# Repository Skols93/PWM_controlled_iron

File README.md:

# PWM_controlled_iron
PCB in Eagle EDA 

Measuring temperature with MAX6675 with Arduino UNO.Using MOSFET to control the temperature of a soldering iron using PID controller implemented in Arduino UNO.

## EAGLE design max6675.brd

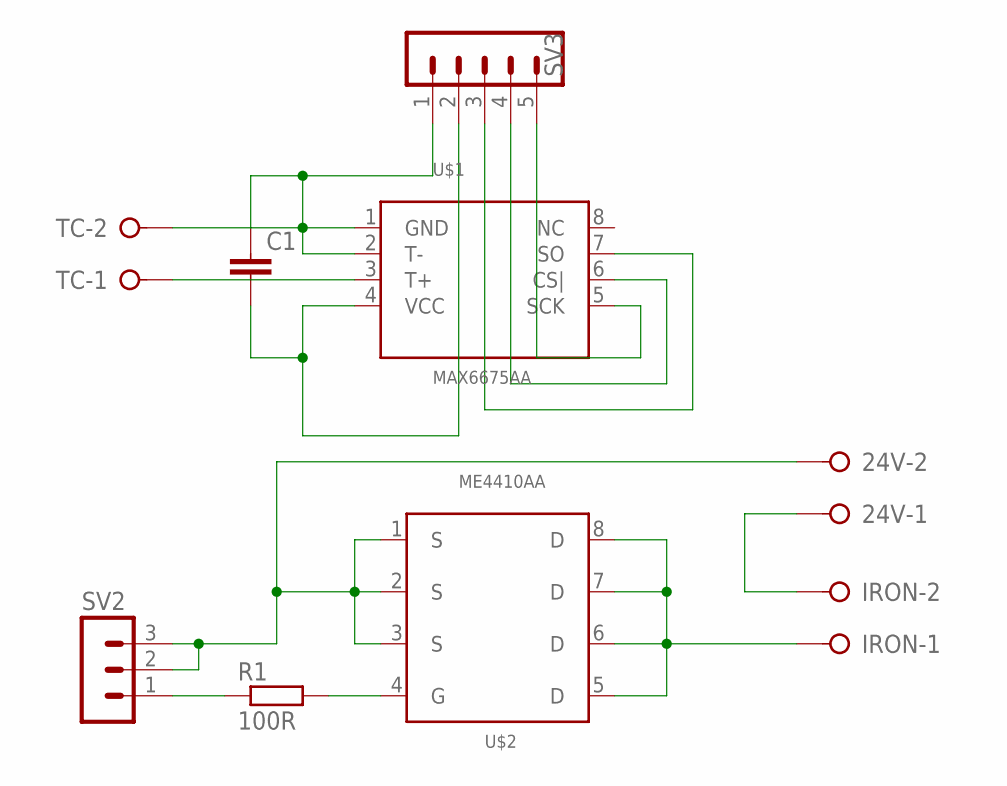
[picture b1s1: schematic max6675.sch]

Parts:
24V: W237-02P; W237-132
C1: C-EU050-025X075; C050-025X075
IRON: W237-02P; W237-132
R1: 100R; M1206
SV2: MA03-1
SV3: MA05-1
TC: W237-02P; W237-132
U$1: MAX6675AA; SO08
U$2: ME4410AA; SO-8

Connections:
unnamed: C1.1, SV3.1, TC.2, U$1.1 (GND), U$1.2 (T-)
unnamed: TC.1, U$1.3 (T+)
unnamed: 24V.2, SV2.2, SV2.3, U$2.1 (S), U$2.2 (S), U$2.3 (S)
unnamed: C1.2, SV3.2, U$1.4 (VCC)
unnamed: SV3.5, U$1.5 (SCK)
unnamed: SV3.4, U$1.6 (CS|)
unnamed: SV3.3, U$1.7 (SO)
unnamed: IRON.1, U$2.5 (D), U$2.6 (D), U$2.7 (D), U$2.8 (D)
unnamed: 24V.1, IRON.2
unnamed: R1.2, U$2.4 (G)
unnamed: R1.1, SV2.1

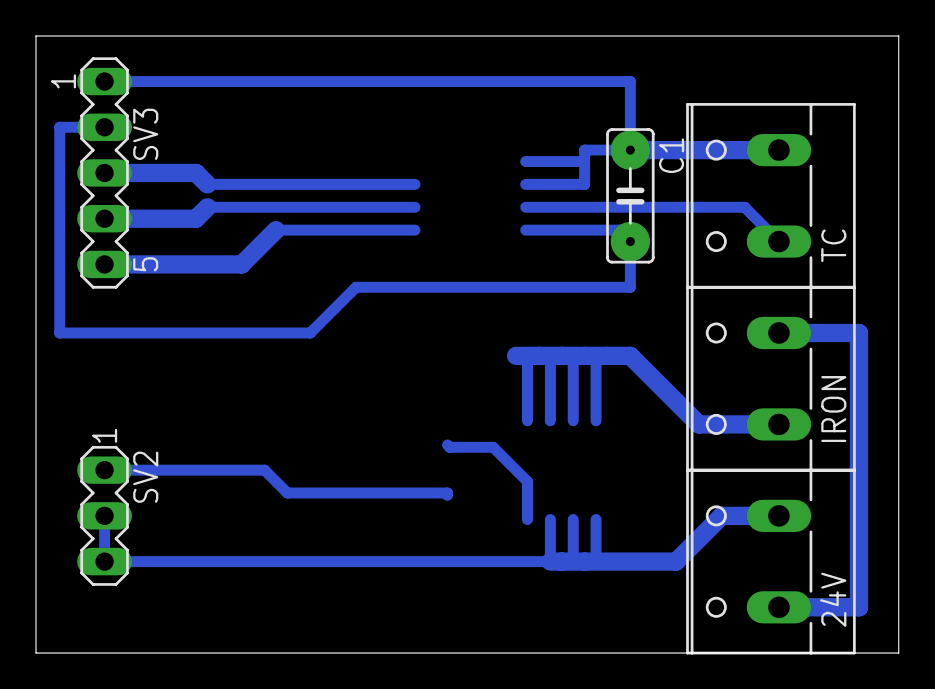
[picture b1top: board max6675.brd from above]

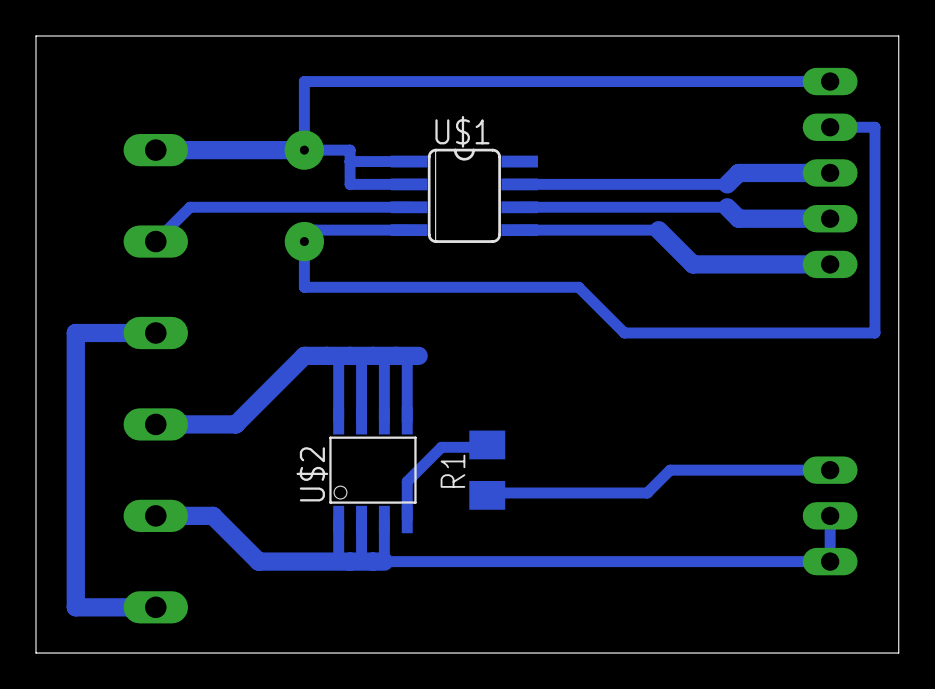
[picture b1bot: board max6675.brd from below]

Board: 2 copper layers, 47.9 x 34.3 mm, 9 parts (3 on the bottom side), 11 nets.

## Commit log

2024-01-20 Eagle PCB, schematic, and library.
